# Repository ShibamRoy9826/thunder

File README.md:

# Thunder ⚡

An FPV RC Car made by myself!

## Features 

None added yet, its a WIP

#### Read my journey of making this project [here](https://github.com/ShibamRoy9826/thunder/JOURNAL.md)

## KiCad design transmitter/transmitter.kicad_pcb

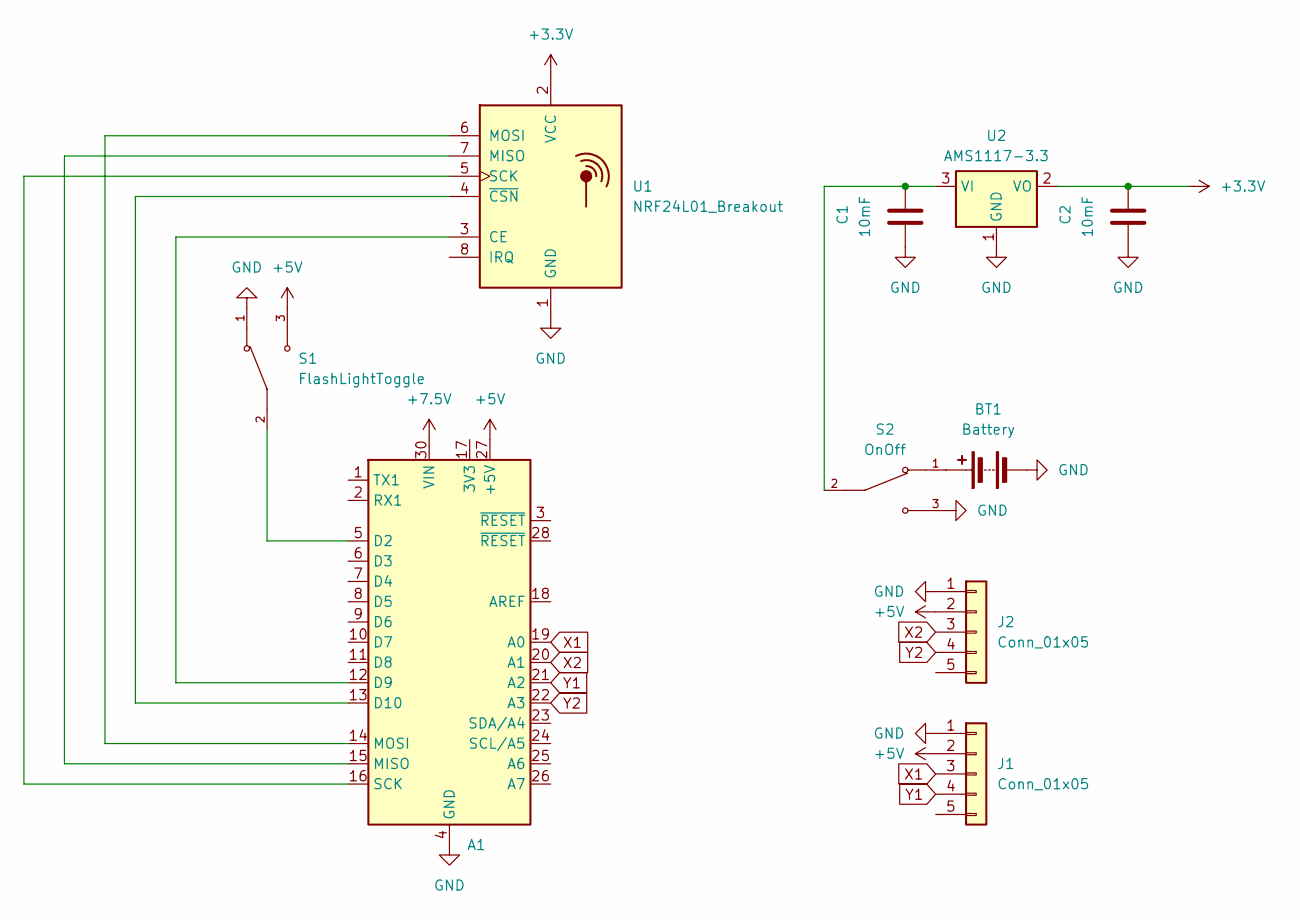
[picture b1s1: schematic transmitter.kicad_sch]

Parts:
A1: Arduino_Nano_Every; Arduino_Nano
BT1: Battery; PinHeader_1x02_P2.54mm_Vertical
C1, C2: 10mF; CP_Radial_D8.0mm_P5.00mm
J1, J2: Conn_01x05; PinHeader_1x05_P2.54mm_Vertical
S1: FlashLightToggle; SW_Slide_SPDT_Straight_CK_OS102011MS2Q; PARTREV E
S2: OnOff; SW_Slide_SPDT_Straight_CK_OS102011MS2Q; PARTREV E
U1: NRF24L01_Breakout; nRF24L01_Breakout
U2: AMS1117-3.3; SOT-223-3_TabPin2

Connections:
+3.3V: C2.2, U1.2 (VCC), U2.2 (VO)
+5V: A1.27 (+5V), J1.2, J2.2, S1.3
+7.5V: A1.30 (VIN)
GND: A1.4 (GND), A1.29 (GND), BT1.2 (-), C1.1, C2.1, J1.1, J2.1, S1.1, S2.3, U1.1 (GND), U2.1 (GND)
unnamed: A1.5 (D2), S1.2
unnamed: A1.12 (D9), U1.3 (CE)
unnamed: A1.13 (D10), U1.4 (~CSN)
unnamed: A1.15 (MISO), U1.7 (MISO)
unnamed: A1.14 (MOSI), U1.6 (MOSI)
unnamed: A1.16 (SCK), U1.5 (SCK)
unnamed: BT1.1 (+), S2.1
unnamed: C1.2, S2.2, U2.3 (VI)
X1: A1.19 (A0), J1.3
X2: A1.20 (A1), J2.3
Y1: A1.21 (A2), J1.4
Y2: A1.22 (A3), J2.4

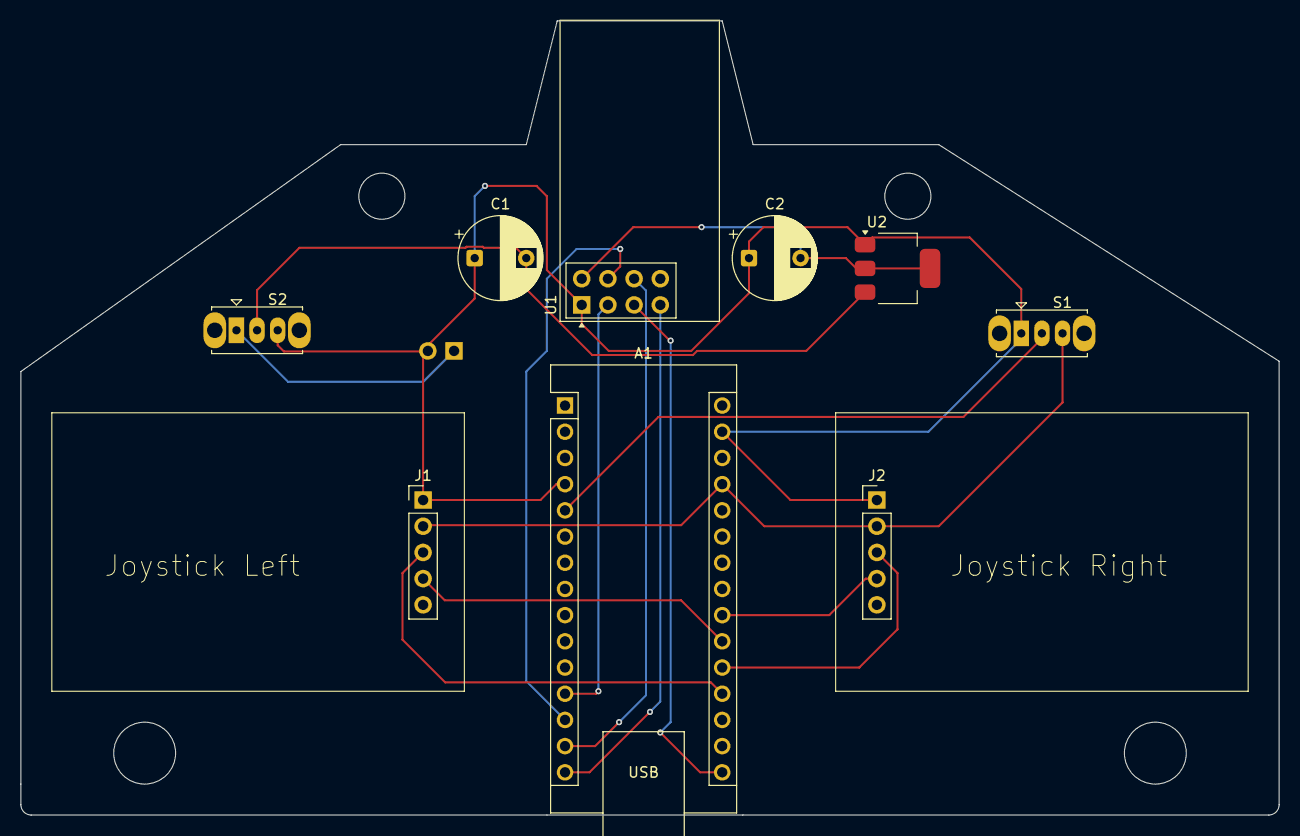
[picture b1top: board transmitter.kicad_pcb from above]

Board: 2 copper layers, 122.0 x 77.0 mm, 10 parts (1 on the bottom side), 15 nets.

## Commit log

2025-05-27 Update journey
2025-05-27 Added readme and fixed some data in journal
2025-05-27 Added transmitter schematic, and fixed readme
2025-05-31 Completed transmitter PCB and rough BOM, updated journal
2025-06-01 Updated BOM, total time spent
